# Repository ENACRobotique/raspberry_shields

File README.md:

# raspberry_shields
Custom shields for raspberrypi

Documentations : 

- [Page wweb raspberrypi](https://www.raspberrypi.com/documentation/computers/raspberry-pi.html)
- [Datasheet BCM2711 ](https://datasheets.raspberrypi.com/bcm2711/bcm2711-peripherals.pdf?_gl=1*1varbtl*_ga*NDYxMjQyMzI5LjE3MTE0NTk1MDc.*_ga_22FD70LWDS*MTcxMTQ1OTUwNi4xLjEuMTcxMTQ1OTY0MS4wLjAuMA..)
 
Les broches des VL53 1 et 2  sont sur des broches pwm

Les uart suivent la norme  Rx, Tx, 3v3, 5v, GND (pdv raspi)

Attention a la configuration PULL UP ou DOWN des gpios ( voir datasheet )

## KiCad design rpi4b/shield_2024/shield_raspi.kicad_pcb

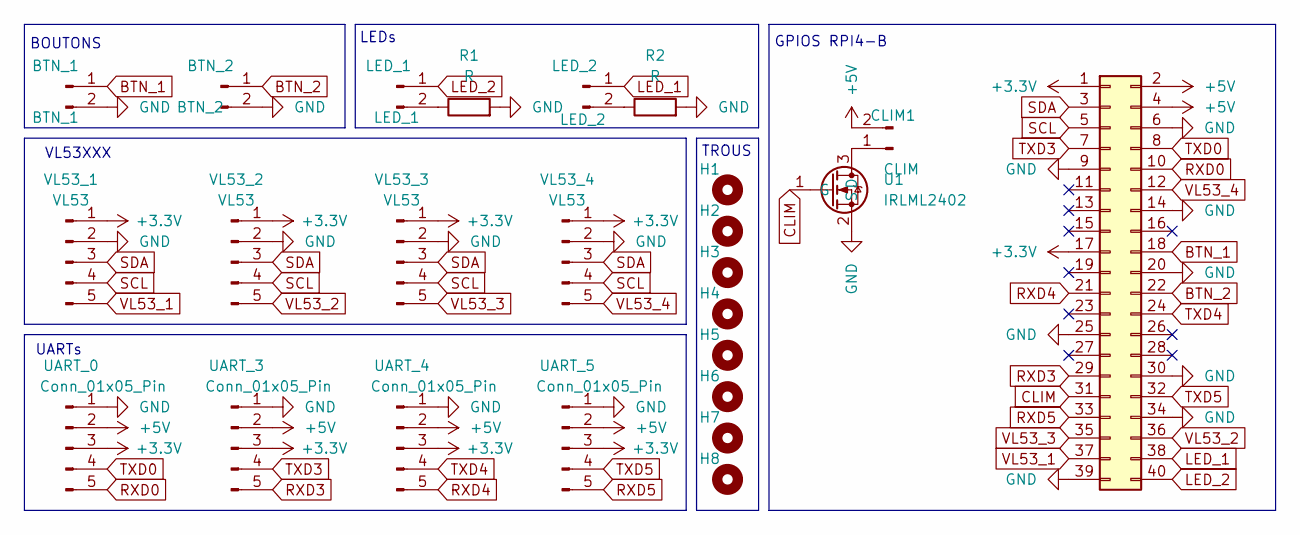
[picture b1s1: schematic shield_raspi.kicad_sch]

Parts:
BTN_1: BTN_1; PinHeader_1x02_P2.54mm_Vertical
BTN_2: BTN_2; PinHeader_1x02_P2.54mm_Vertical
CLIM1: CLIM; PinHeader_1x02_P2.54mm_Vertical
H1, H2, H3, H4, H5, H6, H7, H8: MountingHole; MountingHole_3.2mm_M3
J4: Conn_02x20_Odd_Even; PinSocket_2x20_P2.54mm_Vertical
LED_1: LED_1; PinHeader_1x02_P2.54mm_Vertical
LED_2: LED_2; PinHeader_1x02_P2.54mm_Vertical
R1, R2: R; R_0603_1608Metric
U1: IRLML2402; SOT-23
UART_0, UART_3, UART_4, UART_5: Conn_01x05_Pin; Molex_CLIK-Mate_502382-0570_1x05-1MP_P1.25mm_Vertical
VL53_1, VL53_2, VL53_3, VL53_4: VL53; PinHeader_1x05_P2.54mm_Vertical

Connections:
+3.3V: J4.1, J4.17, UART_0.3, UART_3.3, UART_4.3, UART_5.3, VL53_1.1, VL53_2.1, VL53_3.1, VL53_4.1
+5V: CLIM1.2, J4.2, J4.4, UART_0.2, UART_3.2, UART_4.2, UART_5.2
BTN_1: BTN_1.1, J4.18
BTN_2: BTN_2.1, J4.22
CLIM: J4.31, U1.1 (G)
GND: BTN_1.2, BTN_2.2, J4.6, J4.9, J4.14, J4.20, J4.25, J4.30, J4.34, J4.39, R1.2, R2.2, U1.2 (S), UART_0.1, UART_3.1, UART_4.1, UART_5.1, VL53_1.2, VL53_2.2, VL53_3.2, VL53_4.2
LED_1: J4.38, LED_2.1
LED_2: J4.40, LED_1.1
unnamed: CLIM1.1, U1.3 (D)
unnamed: LED_1.2, R1.1
unnamed: LED_2.2, R2.1
RXD0: J4.10, UART_0.5
RXD3: J4.29, UART_3.5
RXD4: J4.21, UART_4.5
RXD5: J4.33, UART_5.5
SCL: J4.5, VL53_1.4, VL53_2.4, VL53_3.4, VL53_4.4
SDA: J4.3, VL53_1.3, VL53_2.3, VL53_3.3, VL53_4.3
TXD0: J4.8, UART_0.4
TXD3: J4.7, UART_3.4
TXD4: J4.24, UART_4.4
TXD5: J4.32, UART_5.4
VL53_1: J4.37, VL53_1.5
VL53_2: J4.36, VL53_2.5
VL53_3: J4.35, VL53_3.5
VL53_4: J4.12, VL53_4.5

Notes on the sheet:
VL53XXX
UARTs
LEDs
TROUS
BOUTONS
GPIOS RPI4-B

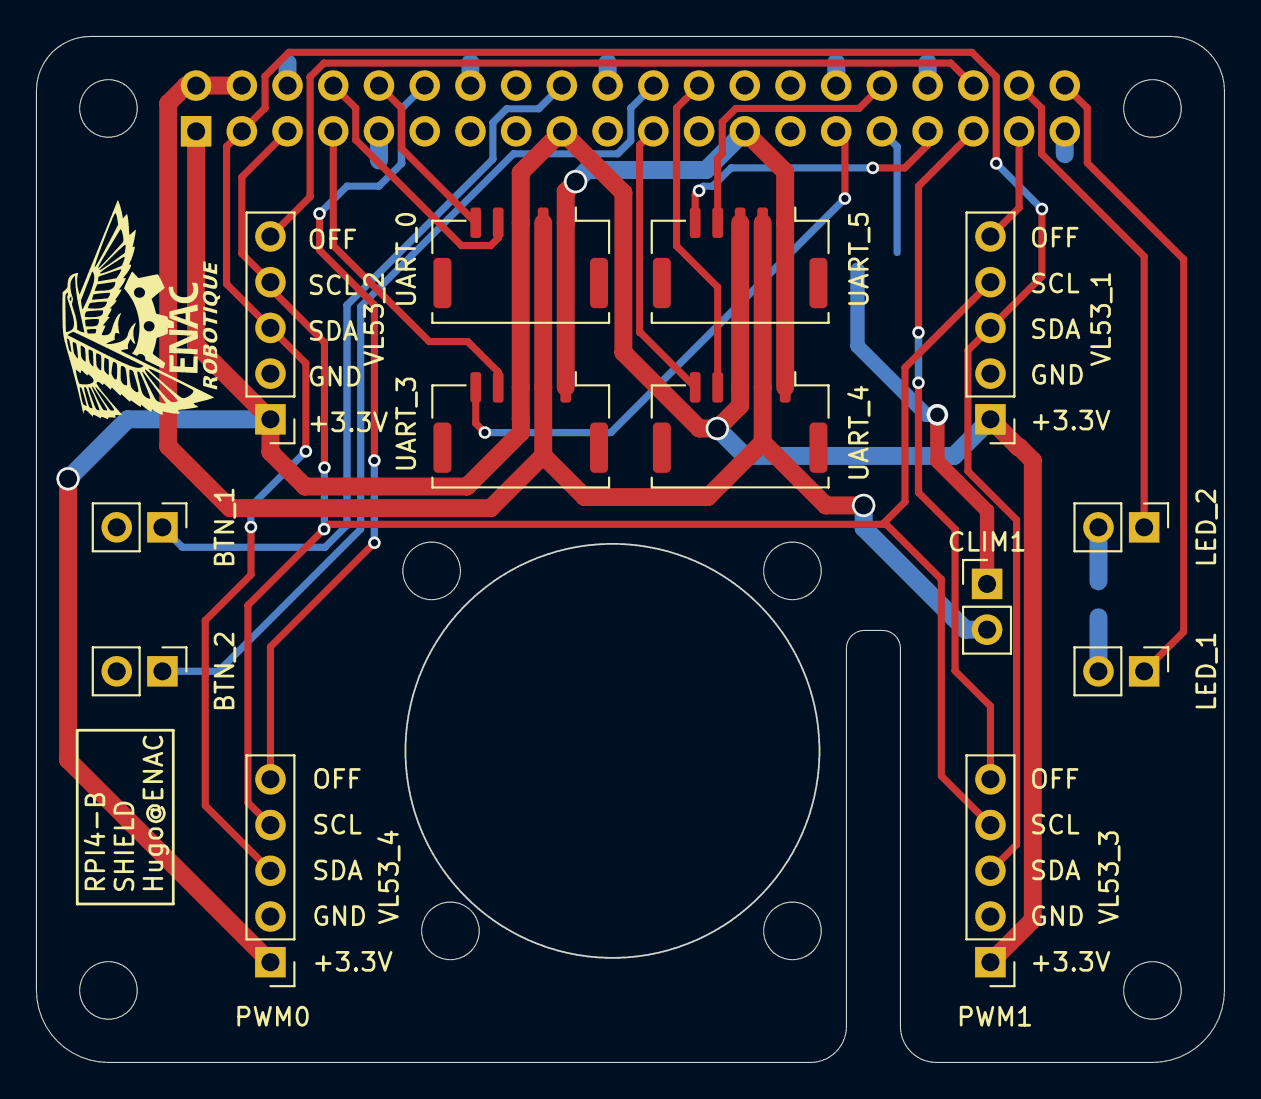
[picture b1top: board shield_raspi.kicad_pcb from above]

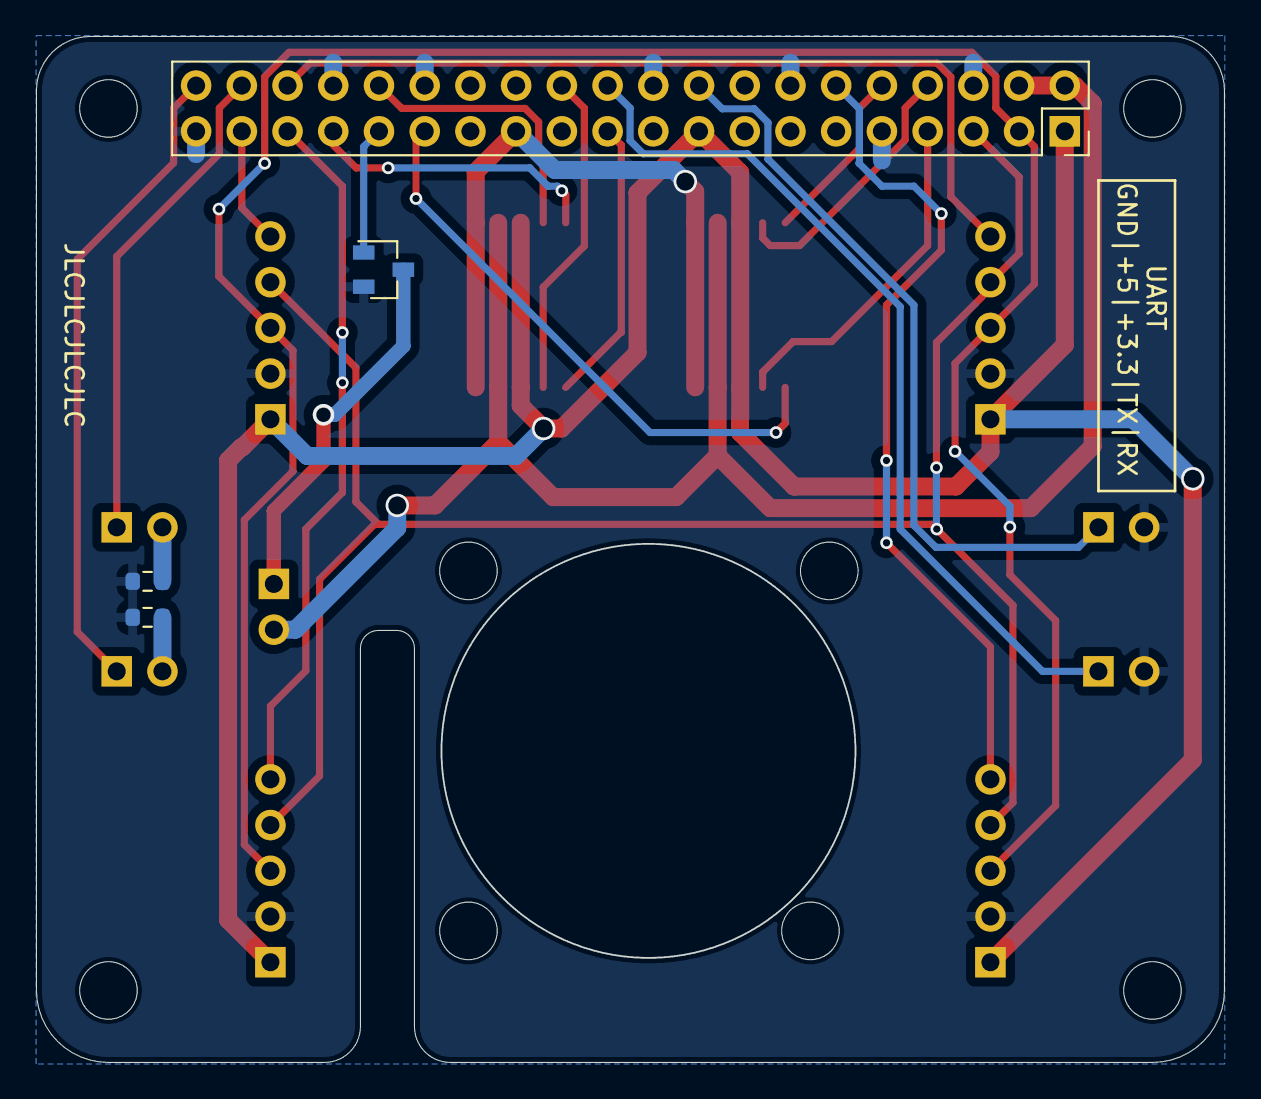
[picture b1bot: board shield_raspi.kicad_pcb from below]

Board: 2 copper layers, 65.9 x 57.0 mm, 25 parts (4 on the bottom side), 25 nets.

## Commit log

2024-03-26 attribution des pins
2024-03-27 placement composant
2024-03-27 routage préliminaire
2024-03-28 DRC okay, ignore Warnings on H1 & H2 , ready to go
2024-03-29 trou ventilateur + molex
2024-04-02 Validation en attente + Add uarts, ventillo
2024-04-02 WIP le ventillo
2024-04-03 ajout clim , attente de validation
2024-04-07 trou caméra
2024-04-08 release V1
2024-04-19 modif avec destruction physique
